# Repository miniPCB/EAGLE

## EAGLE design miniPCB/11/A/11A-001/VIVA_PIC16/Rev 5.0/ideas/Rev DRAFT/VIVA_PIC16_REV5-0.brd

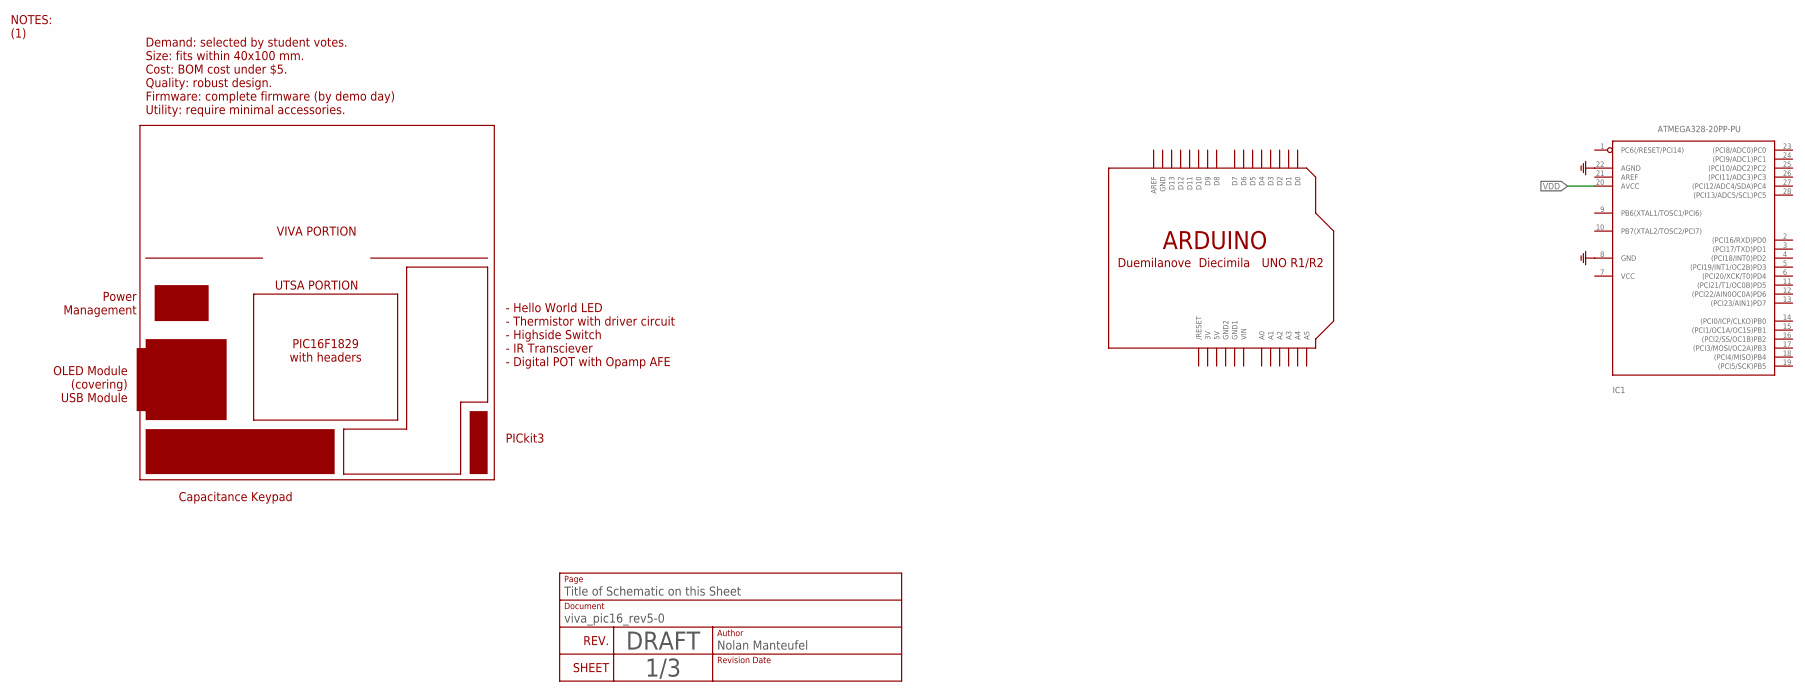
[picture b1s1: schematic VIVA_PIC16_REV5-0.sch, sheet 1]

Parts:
IC1: ATMEGA328-20PP-PU; DIL28-3
U$1: VIVA_LOGO
U$3: ARDUINOUNO; ARDUINO

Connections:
3V: U$3.3V
5V: U$3.5V
GND: IC1.8 (GND), IC1.22 (AGND), U$3.GND; also elsewhere on the board
GND1: U$3.GND1
GND2: U$3.GND2
VDD: IC1.20 (AVCC); also elsewhere on the board
VIN: U$3.VIN

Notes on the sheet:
REV.
DRAFT
Revision Date
Author
SHEET
Document
Title of Schematic on this Sheet
Page
Nolan Manteufel
NOTES: (1)
UTSA PORTION
VIVA PORTION
Demand: selected by student votes. Size: fits within 40x100 mm. Cost: BOM cost under $5. Quality: robust design. Firmware: complete firmware (by demo day) Utility: require minimal accessories.
OLED Module (covering) USB Module
Power Management
Capacitance Keypad
PICkit3
PIC16F1829 with headers
- Hello World LED - Thermistor with driver circuit - Highside Switch - IR Transciever - Digital POT with Opamp AFE

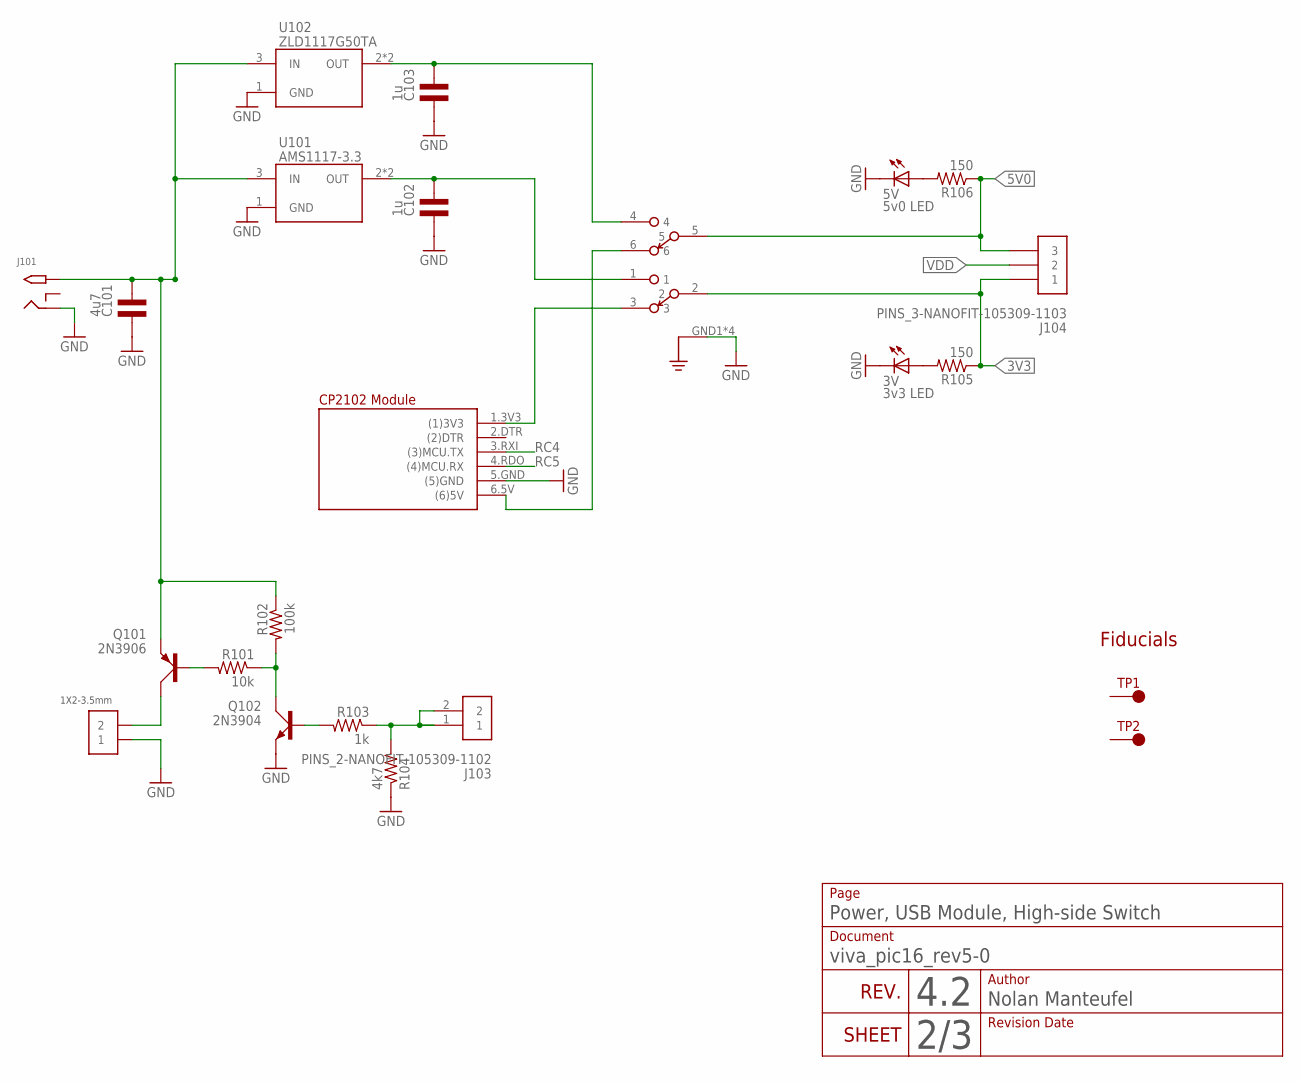
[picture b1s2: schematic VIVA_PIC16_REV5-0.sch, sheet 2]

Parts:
3V: 3v3 LED; CHIPLED_0805
5V: 5v0 LED; CHIPLED_0805
C101: 4u7; C0805
C102, C103: 1u; C0805
J101: 2.1MMJACKTHM; PJ-102A
J102: 1X2-3.5MM-3.5MM; 1X2-3.5MM
J103: PINS_2-NANOFIT-105309-1102; PINS_2-NANOFIT
J104: PINS_3-NANOFIT-105309-1103; PINS_3-NANOFIT
M101: VIVA_USB-TTL; VIVA_USB_TTL_SUBTEXT
Q101: 2N3906; SOT23
Q102: 2N3904; SOT23
R101: 10k; R0805
R102: 100k; R0805
R103: 1k; R0805
R104: 4k7; R0805
R105, R106: 150; R0805
S101: SWITCH_OS202013; OS202013MT5QN1
TP1, TP2: TESTPOINTFIDUCIAL; FIDUCIAL
U101: AMS1117-3.3; SOT223
U102: ZLD1117G50TA; SOT223

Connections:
3V3: J104.1, R105.1, S101.2
5V0: J104.3, R106.1, S101.5
GND: 3V.C, 5V.C, C101.1, C102.1, C103.1, J101.RING, J102.1, M101.5.GND ((5)GND), Q102.2 (E), R104.1, S101.GND1 (GND), S101.GND2 (GND), S101.GND3 (GND), S101.GND4 (GND), U101.1 (GND), U102.1 (GND); also elsewhere on the board
unnamed: J103.1, J103.2, R103.1, R104.2
unnamed: 5V.A, R106.2
unnamed: Q101.1 (B), R101.2
unnamed: Q102.3 (C), R101.1, R102.2
unnamed: Q102.1 (B), R103.2
unnamed: M101.1.3V3 ((1)3V3), S101.3
unnamed: J102.2, Q101.3 (C)
unnamed: M101.6.5V ((6)5V), S101.6
unnamed: C103.2, S101.4, U102.2 (OUT), U102.4.TAB (OUT)
unnamed: C102.2, S101.1, U101.2 (OUT), U101.4.TAB (OUT)
unnamed: 3V.A, R105.2
RC4: M101.3.RXI ((3)MCU.TX); also elsewhere on the board
RC5: M101.4.RDO ((4)MCU.RX); also elsewhere on the board
VDC: C101.2, J101.TIP, Q101.2 (E), R102.1, U101.3 (IN), U102.3 (IN)
VDD: J104.2; also elsewhere on the board

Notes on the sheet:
REV.
4.2
Revision Date
Author
SHEET
Document
Power, USB Module, High-side Switch
Page
Nolan Manteufel
Fiducials

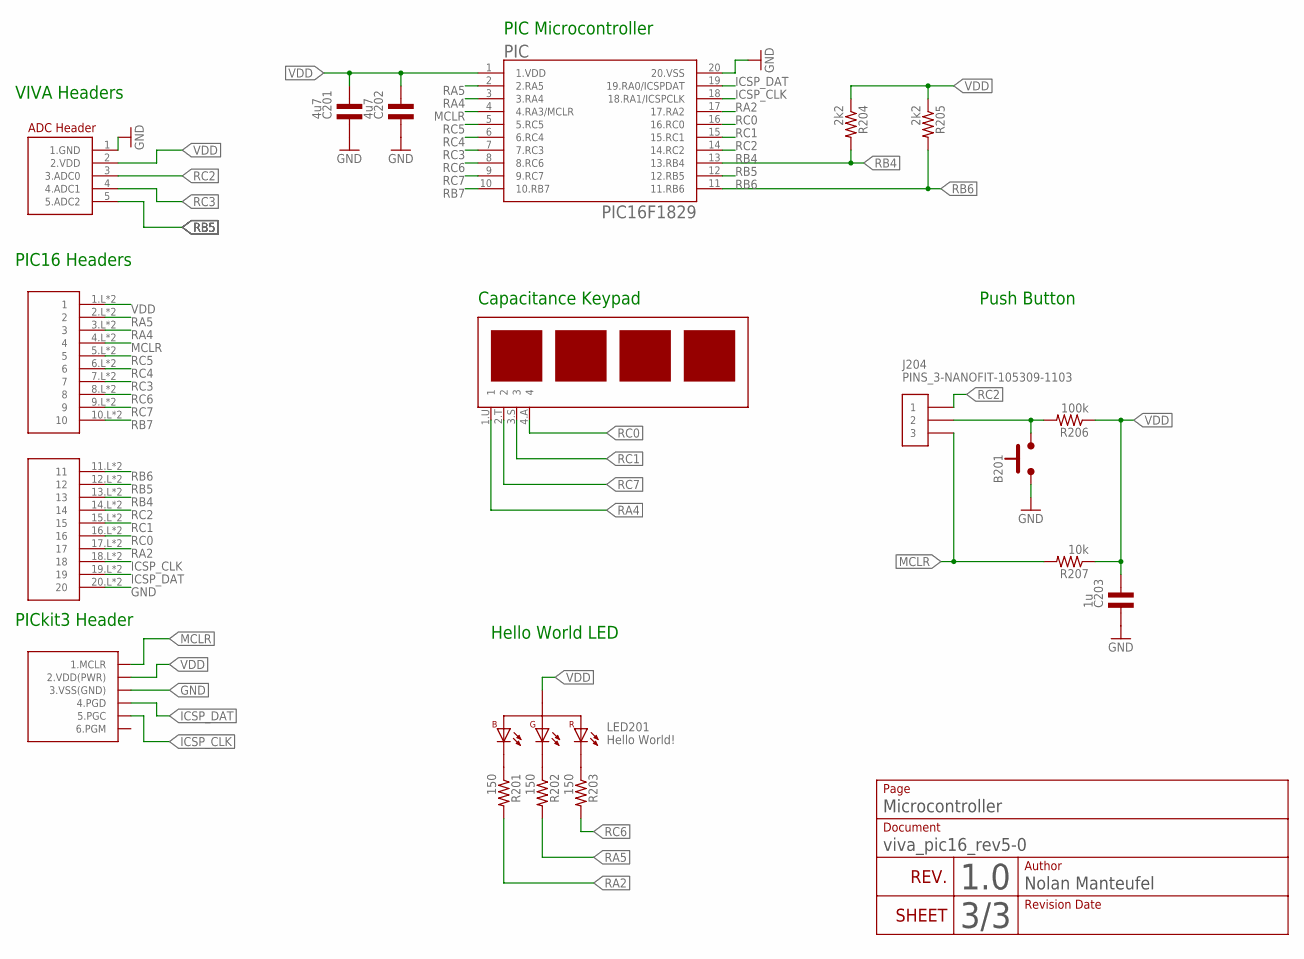
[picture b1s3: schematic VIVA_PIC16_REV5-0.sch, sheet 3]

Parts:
B201: PUSHBUTTON6X6MM; 6X6MM
C201, C202: 4u7; C0805
C203: 1u; C0805
J201: VIVA_PIC16
J202: VIVA-HEADER-ADCNONAME; VIVA-HEADER-ADC-NONAME
J203: PICKIT3
J204: PINS_3-NANOFIT-105309-1103; PINS_3-NANOFIT
LED201: Hello World!; 0805_RGB
PIC: PIC16F1829; SOP20-NEW
R201, R202, R203: 150; R0805
R204, R205: 2k2; R0805
R206: 100k; R0805
R207: 10k; R0805
U$201: VIVA_UTSA-KEYPAD

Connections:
GND: B201.1.A (1), B201.2.A (1), C201.1, C202.1, C203.1, J201.20.L (20), J201.20.R (20), J202.1 (1.GND), J203.3 (3.VSS(GND)), PIC.20 (20.VSS); also elsewhere on the board
ICSP_CLK: J201.18.L (18), J201.18.R (18), J203.5 (5.PGC), PIC.18 (18.RA1/ICSPCLK)
ICSP_DAT: J201.19.L (19), J201.19.R (19), J203.4 (4.PGD), PIC.19 (19.RA0/ICSPDAT)
MCLR: J201.4.L (4), J201.4.R (4), J203.1 (1.MCLR), J204.3, PIC.4 (4.RA3/MCLR), R207.2
unnamed: B201.3.B (2), B201.4.B (2), J204.2, R206.2
unnamed: LED201.1 (4.B-), R201.1
unnamed: LED201.3 (2.G-), R202.1
unnamed: LED201.2 (1.R-), R203.1
RA2: J201.17.L (17), J201.17.R (17), PIC.17 (17.RA2), R201.2
RA4: J201.3.L (3), J201.3.R (3), PIC.3 (3.RA4), U$201.1.U (1)
RA5: J201.2.L (2), J201.2.R (2), PIC.2 (2.RA5), R202.2
RB4: J201.13.L (13), J201.13.R (13), PIC.13 (13.RB4), R204.2
RB5: J201.12.L (12), J201.12.R (12), J202.5 (5.ADC2), PIC.12 (12.RB5)
RB6: J201.11.L (11), J201.11.R (11), PIC.11 (11.RB6), R205.2
RB7: J201.10.L (10), J201.10.R (10), PIC.10 (10.RB7)
RC0: J201.16.L (16), J201.16.R (16), PIC.16 (16.RC0), U$201.4.A (4)
RC1: J201.15.L (15), J201.15.R (15), PIC.15 (15.RC1), U$201.3.S (3)
RC2: J201.14.L (14), J201.14.R (14), J202.3 (3.ADC0), J204.1, PIC.14 (14.RC2)
RC3: J201.7.L (7), J201.7.R (7), J202.4 (4.ADC1), PIC.7 (7.RC3)
RC4: J201.6.L (6), J201.6.R (6), PIC.6 (6.RC4); also elsewhere on the board
RC5: J201.5.L (5), J201.5.R (5), PIC.5 (5.RC5); also elsewhere on the board
RC6: J201.8.L (8), J201.8.R (8), PIC.8 (8.RC6), R203.2
RC7: J201.9.L (9), J201.9.R (9), PIC.9 (9.RC7), U$201.2.T (2)
VDD: C201.2, C202.2, C203.2, J201.1.L (1), J201.1.R (1), J202.2 (2.VDD), J203.2 (2.VDD(PWR)), LED201.4 (3.+), PIC.1 (1.VDD), R204.1, R205.1, R206.1, R207.1; also elsewhere on the board

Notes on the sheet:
REV.
1.0
Revision Date
Author
SHEET
Document
Microcontroller
Page
Nolan Manteufel
Push Button
Hello World LED
PICkit3 Header
PIC Microcontroller
VIVA Headers
PIC16 Headers
Capacitance Keypad

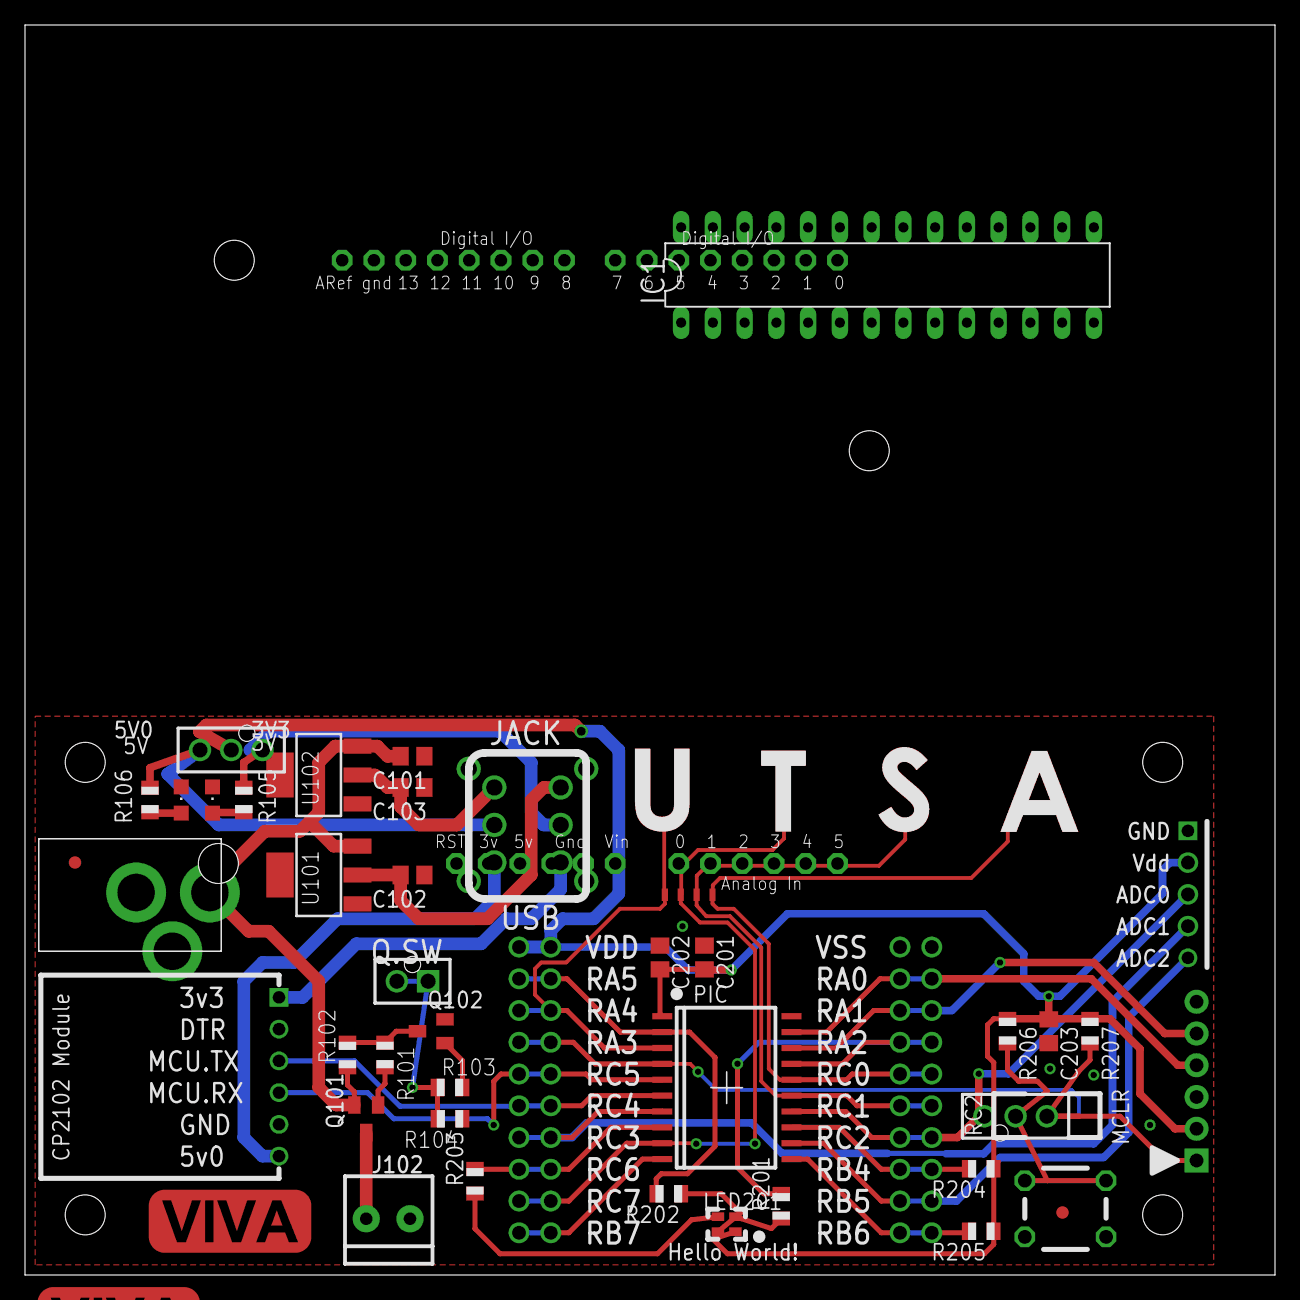
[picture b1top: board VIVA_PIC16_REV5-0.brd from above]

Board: 2 copper layers, 100.0 x 100.0 mm, 45 parts (0 on the bottom side), 38 nets.

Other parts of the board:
U$2: VIVA_LOGO

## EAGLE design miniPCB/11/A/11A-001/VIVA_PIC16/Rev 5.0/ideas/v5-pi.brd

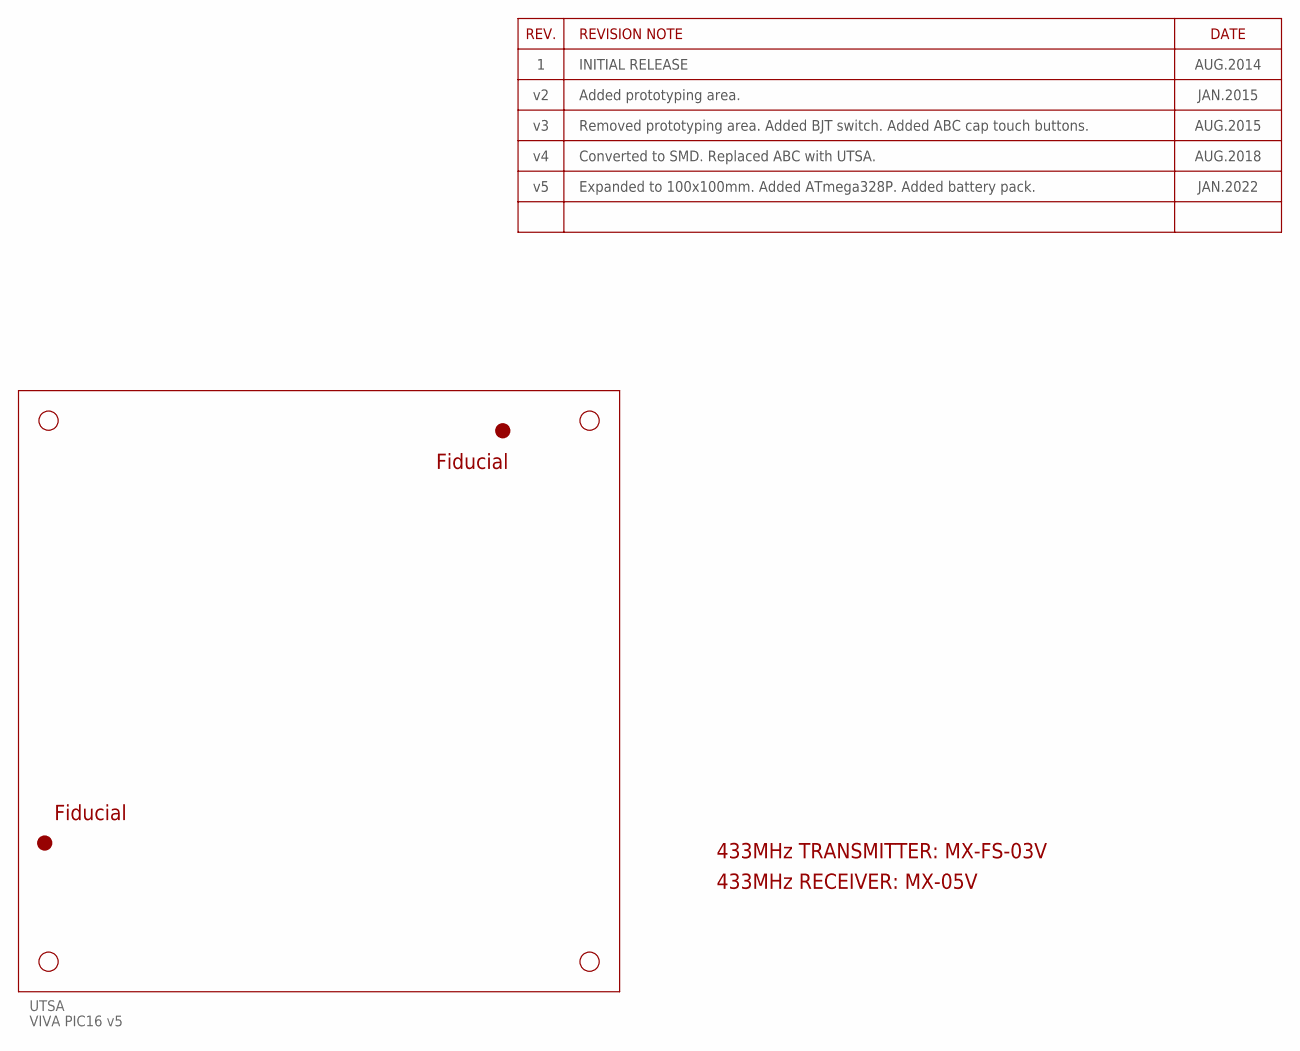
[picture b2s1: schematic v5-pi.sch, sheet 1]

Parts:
FIDUCIAL1, FIDUCIAL2: FIDUCIAL
UTSA: VIVA PIC16 v5; PCB_100X100

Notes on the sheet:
Fiducial
433MHz TRANSMITTER: MX-FS-03V
433MHz RECEIVER: MX-05V

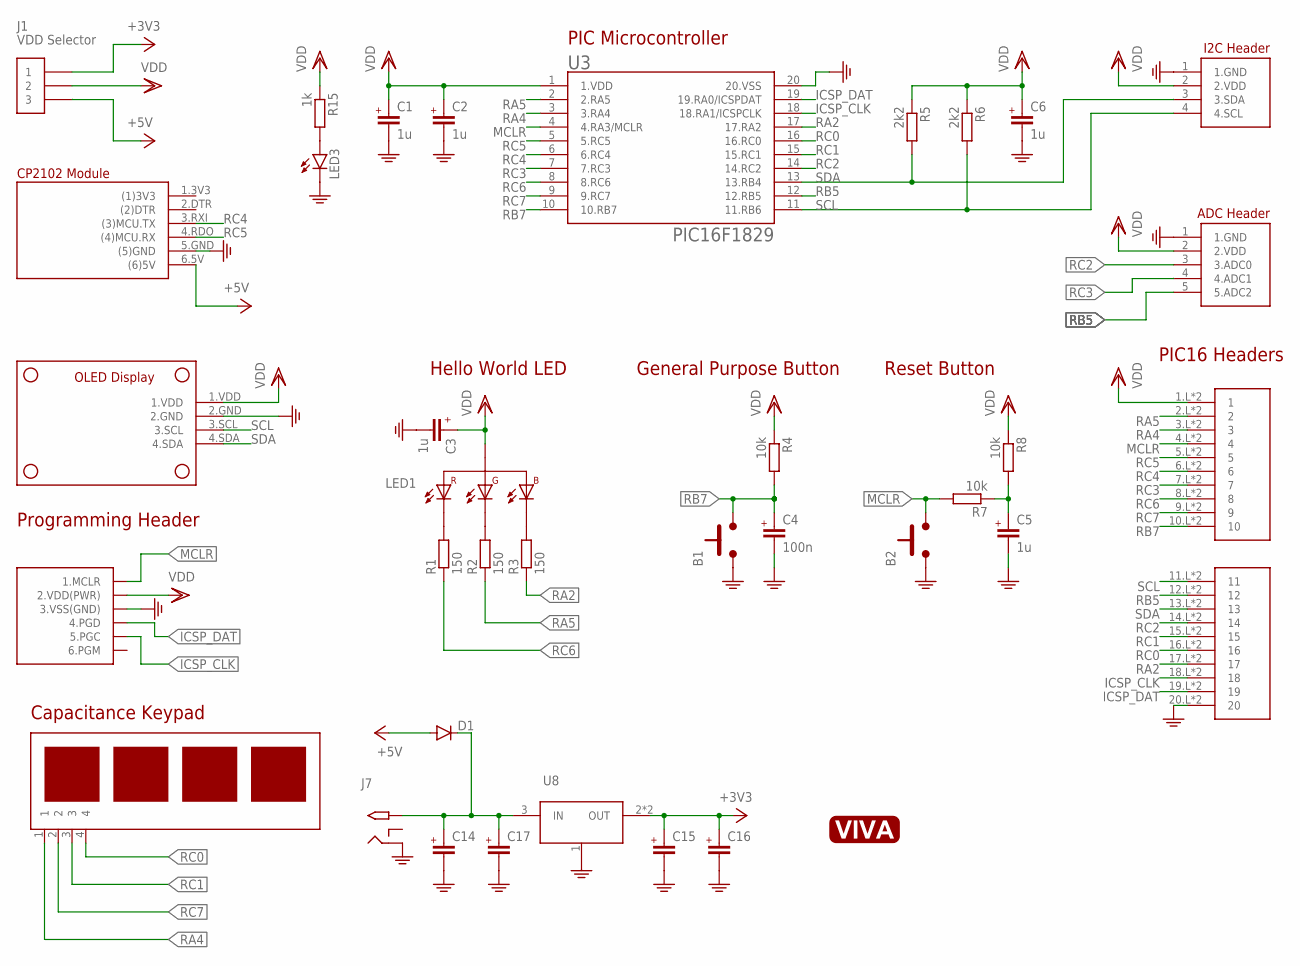
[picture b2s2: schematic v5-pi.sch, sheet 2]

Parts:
B1, B2: PUSHBUTTON6X6MM; 6X6MM
C1, C2, C3, C5, C6: 1u; C0805
C4: 100n; C0805
C14, C15, C16, C17: C0805
D1: DIODE-DO214AC; DO214AC
J1: VDD Selector; PINS_3
J4: PICKIT3
J5: VIVA-HEADER-ADC-PIC16
J7: 2.1MMJACKTHM; PJ-102A
LED1: LED_RGBLTST-C19FD1WT; 0805_RGB
LED3: LEDSML0805; SML0805
R1, R2, R3: 150; R0805
R4, R7, R8: 10k; R0805
R5, R6: 2k2; R0805
R15: 1k; R0805
U1: VIVA_UTSA-KEYPADV5; VIVA_UTSA-KEYPAD-V5
U2: VIVA_USB-TTL; VIVA_USB_TTL_SUBTEXT
U3: PIC16F1829; SOP20-NEW
U4: VIVA-HEADER-I2C-RA
U5: VIVA_PIC16BOARD; VIVA_PIC16
U8: REGULATOR_SCHLM1117; SOT223
U$2: VIVA_LOGO
U$3: VIVA_OLED; VIVA_OLED-I2C

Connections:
+3V3: C15.2 (+), C16.2 (+), J1.1, U8.2 (OUT), U8.4.TAB (OUT)
+5V: D1.A, J1.3, U2.6.5V ((6)5V); also elsewhere on the board
GND: B1.1.A (1), B1.2.A (1), B2.1.A (1), B2.2.A (1), C1.1 (-), C2.1 (-), C3.1 (-), C4.1 (-), C5.1 (-), C6.1 (-), C14.1 (-), C15.1 (-), C16.1 (-), C17.1 (-), J4.3 (3.VSS(GND)), J5.1 (1.GND), J7.RING, LED3.C, U2.5.GND ((5)GND), U3.20 (20.VSS), U4.1 (1.GND), U5.20.L (20), U5.20.R (20), U8.1 (GND), U$3.2.GND; also elsewhere on the board
ICSP_CLK: J4.5 (5.PGC), U3.18 (18.RA1/ICSPCLK), U5.18.L (18), U5.18.R (18)
ICSP_DAT: J4.4 (4.PGD), U3.19 (19.RA0/ICSPDAT), U5.19.L (19), U5.19.R (19)
MCLR: B2.3.B (2), B2.4.B (2), J4.1 (1.MCLR), R7.2, U3.4 (4.RA3/MCLR), U5.4.L (4), U5.4.R (4)
MCLR_CAP: C5.2 (+), R7.1, R8.2
unnamed: LED1.2 (1.R-), R1.2
unnamed: LED1.3 (2.G-), R2.2
unnamed: LED1.1 (4.B-), R3.2
unnamed: C14.2 (+), C17.2 (+), D1.C, J7.TIP, U8.3 (IN)
unnamed: LED3.A, R15.2
RA2: R3.1, U3.17 (17.RA2), U5.17.L (17), U5.17.R (17)
RA4: U1.1, U3.3 (3.RA4), U5.3.L (3), U5.3.R (3)
RA5: R2.1, U3.2 (2.RA5), U5.2.L (2), U5.2.R (2)
RB5: J5.5 (5.ADC2), U3.12 (12.RB5), U5.12.L (12), U5.12.R (12)
RB7: B1.3.B (2), B1.4.B (2), C4.2 (+), R4.2, U3.10 (10.RB7), U5.10.L (10), U5.10.R (10)
RC0: U1.4, U3.16 (16.RC0), U5.16.L (16), U5.16.R (16)
RC1: U1.3, U3.15 (15.RC1), U5.15.L (15), U5.15.R (15)
RC2: J5.3 (3.ADC0), U3.14 (14.RC2), U5.14.L (14), U5.14.R (14)
RC3: J5.4 (4.ADC1), U3.7 (7.RC3), U5.7.L (7), U5.7.R (7)
RC4: U2.3.RXI ((3)MCU.TX), U3.6 (6.RC4), U5.6.L (6), U5.6.R (6)
RC5: U2.4.RDO ((4)MCU.RX), U3.5 (5.RC5), U5.5.L (5), U5.5.R (5)
RC6: R1.1, U3.8 (8.RC6), U5.8.L (8), U5.8.R (8)
RC7: U1.2, U3.9 (9.RC7), U5.9.L (9), U5.9.R (9)
SCL: R6.2, U3.11 (11.RB6), U4.4 (4.SCL), U5.11.L (11), U5.11.R (11), U$3.3.SCL; also elsewhere on the board
SDA: R5.2, U3.13 (13.RB4), U4.3 (3.SDA), U5.13.L (13), U5.13.R (13), U$3.4.SDA; also elsewhere on the board
VDD: C1.2 (+), C2.2 (+), C3.2 (+), C6.2 (+), J1.2, J4.2 (2.VDD(PWR)), J5.2 (2.VDD), LED1.4 (3.+), R4.1, R5.1, R6.1, R8.1, R15.1, U3.1 (1.VDD), U4.2 (2.VDD), U5.1.L (1), U5.1.R (1), U$3.1.VDD; also elsewhere on the board

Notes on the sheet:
General Purpose Button
Hello World LED
PIC Microcontroller
Capacitance Keypad
Reset Button
Programming Header
PIC16 Headers

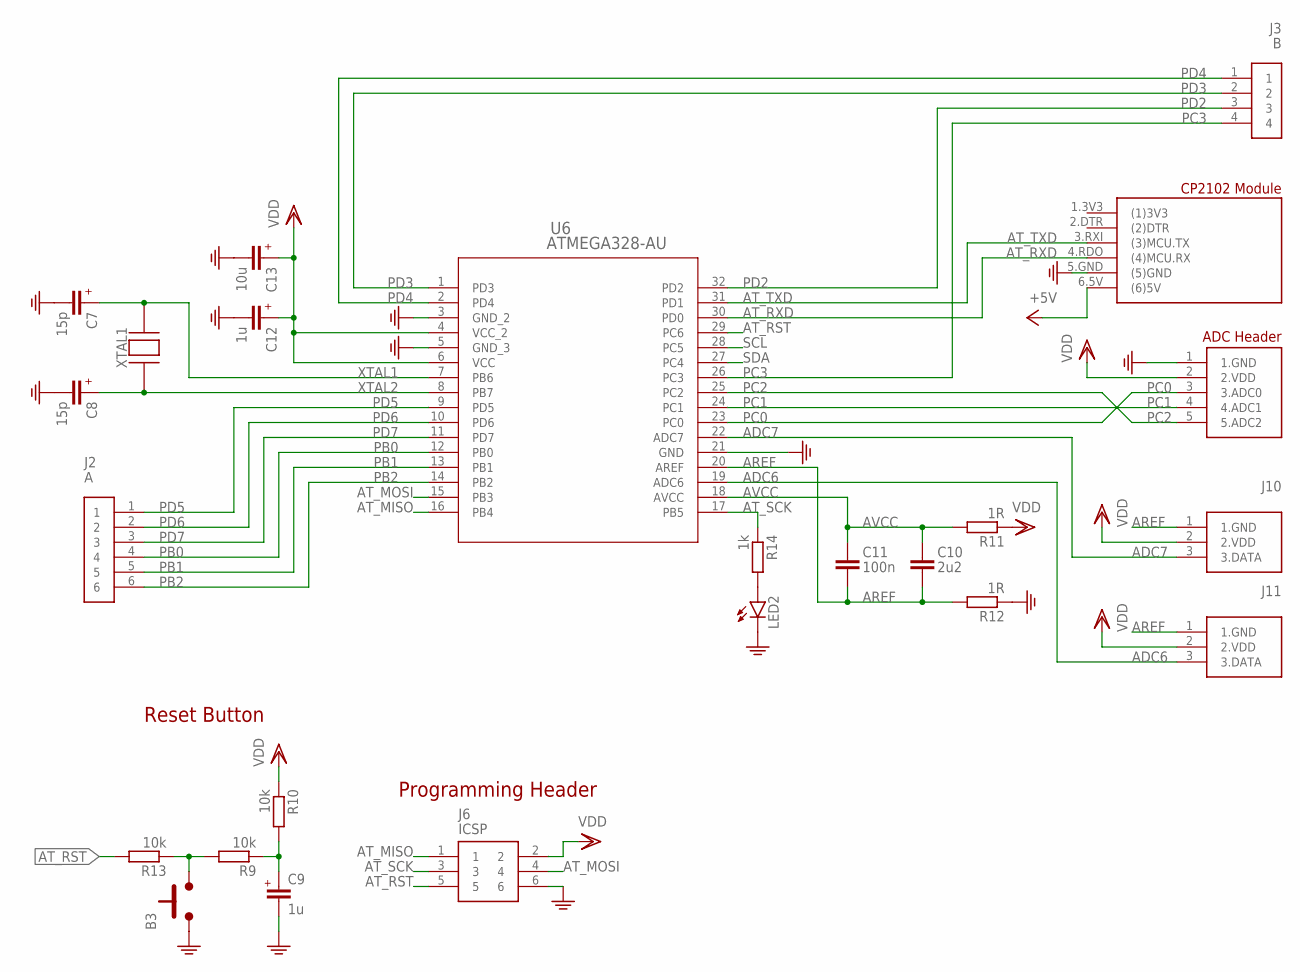
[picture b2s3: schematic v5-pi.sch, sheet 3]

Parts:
B3: PUSHBUTTON6X6MM; 6X6MM
C7, C8: 15p; C0603
C9, C12: 1u; C0805
C10: 2u2; C0805
C11: 100n; C0805
C13: 10u; C0805
J2: A; PINS_6
J3: B; PINS_4
J6: ICSP; PINS_6-2X3
J9: VIVA-HEADER-ADC-PIC16
J10, J11: VIVA-HEADER-GPIO-1; VIVA-HEADER-GPIO-RA-1
LED2: LEDSML0805; SML0805
R9, R10, R13: 10k; R0805
R11, R12: 1R; R0805
R14: 1k; R0805
U6: ATMEGA328-AU; 32A_ATM
U7: VIVA_USB-TTL; VIVA_USB_TTL_SUBTEXT
XTAL1: CRYSTAL-SMD; HC49S-SMD

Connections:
+5V: U7.6.5V ((6)5V); also elsewhere on the board
ADC6: J11.3 (3.DATA), U6.19 (ADC6)
ADC7: J10.3 (3.DATA), U6.22 (ADC7)
AREF: C10.2, C11.2, J10.1 (1.GND), J11.1 (1.GND), R12.2, U6.20 (AREF)
AT_MISO: J6.1, U6.16 (PB4)
AT_MOSI: J6.4, U6.15 (PB3)
AT_RST: J6.5, R13.2, U6.29 (PC6)
AT_RST_BTN: B3.3.B (2), B3.4.B (2), R9.2, R13.1
AT_RST_CAP: C9.2 (+), R9.1, R10.2
AT_RXD: U6.30 (PD0), U7.4.RDO ((4)MCU.RX)
AT_SCK: J6.3, R14.1, U6.17 (PB5)
AT_TXD: U6.31 (PD1), U7.3.RXI ((3)MCU.TX)
AVCC: C10.1, C11.1, R11.2, U6.18 (AVCC)
GND: B3.1.A (1), B3.2.A (1), C7.1 (-), C8.1 (-), C9.1 (-), C12.1 (-), C13.1 (-), J6.6, J9.1 (1.GND), LED2.C, R12.1, U6.3 (GND_2), U6.5 (GND_3), U6.21 (GND), U7.5.GND ((5)GND); also elsewhere on the board
unnamed: LED2.A, R14.2
PB0: J2.4, U6.12 (PB0)
PB1: J2.5, U6.13 (PB1)
PB2: J2.6, U6.14 (PB2)
PC0: J9.3 (3.ADC0), U6.23 (PC0)
PC1: J9.4 (4.ADC1), U6.24 (PC1)
PC2: J9.5 (5.ADC2), U6.25 (PC2)
PC3: J3.4, U6.26 (PC3)
PD2: J3.3, U6.32 (PD2)
PD3: J3.2, U6.1 (PD3)
PD4: J3.1, U6.2 (PD4)
PD5: J2.1, U6.9 (PD5)
PD6: J2.2, U6.10 (PD6)
PD7: J2.3, U6.11 (PD7)
SCL: U6.28 (PC5); also elsewhere on the board
SDA: U6.27 (PC4); also elsewhere on the board
VDD: C12.2 (+), C13.2 (+), J6.2, J9.2 (2.VDD), J10.2 (2.VDD), J11.2 (2.VDD), R10.1, R11.1, U6.4 (VCC_2), U6.6 (VCC); also elsewhere on the board
XTAL1: C7.2 (+), U6.7 (PB6), XTAL1.2, XTAL1.4 (2)
XTAL2: C8.2 (+), U6.8 (PB7), XTAL1.1, XTAL1.3 (1)

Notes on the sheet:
Reset Button
Programming Header

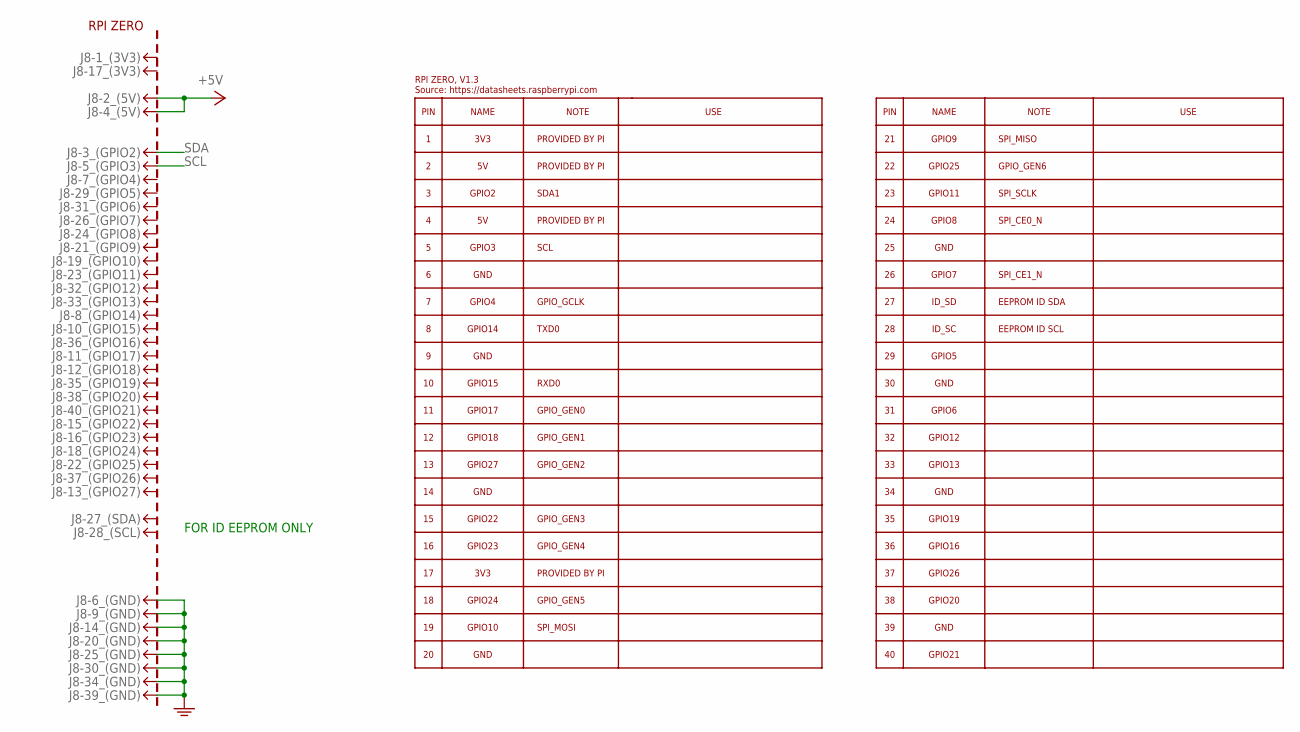
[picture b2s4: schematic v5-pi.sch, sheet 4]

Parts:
J8-: RPI ZERO; RPI_ZERO

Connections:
+5V: J8-.2, J8-.4; also elsewhere on the board
GND: J8-.6, J8-.9, J8-.14, J8-.20, J8-.25, J8-.30, J8-.34, J8-.39; also elsewhere on the board
SCL: J8-.5; also elsewhere on the board
SDA: J8-.3; also elsewhere on the board

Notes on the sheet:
FOR ID EEPROM ONLY

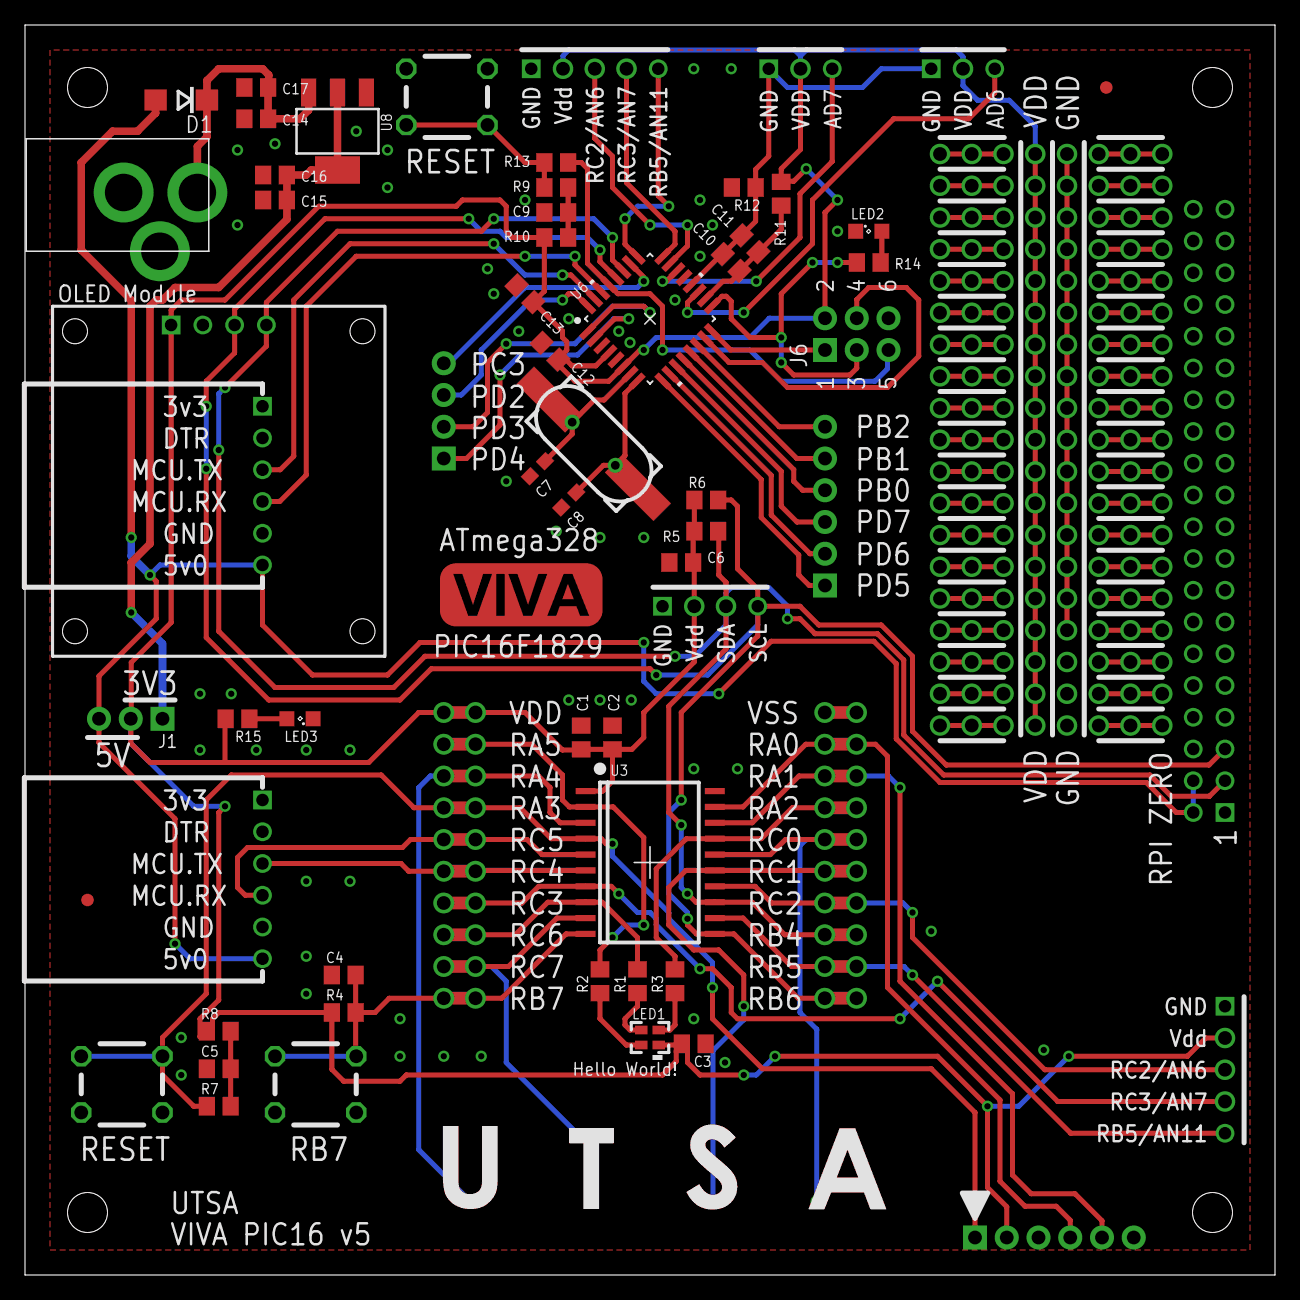
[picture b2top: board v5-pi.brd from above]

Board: 4 copper layers, 100.0 x 100.0 mm, 64 parts (0 on the bottom side), 56 nets.

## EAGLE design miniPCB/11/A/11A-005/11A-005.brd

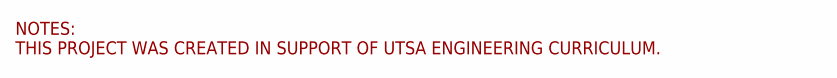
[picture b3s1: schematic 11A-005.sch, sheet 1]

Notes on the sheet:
NOTES: THIS PROJECT WAS CREATED IN SUPPORT OF UTSA ENGINEERING CURRICULUM.

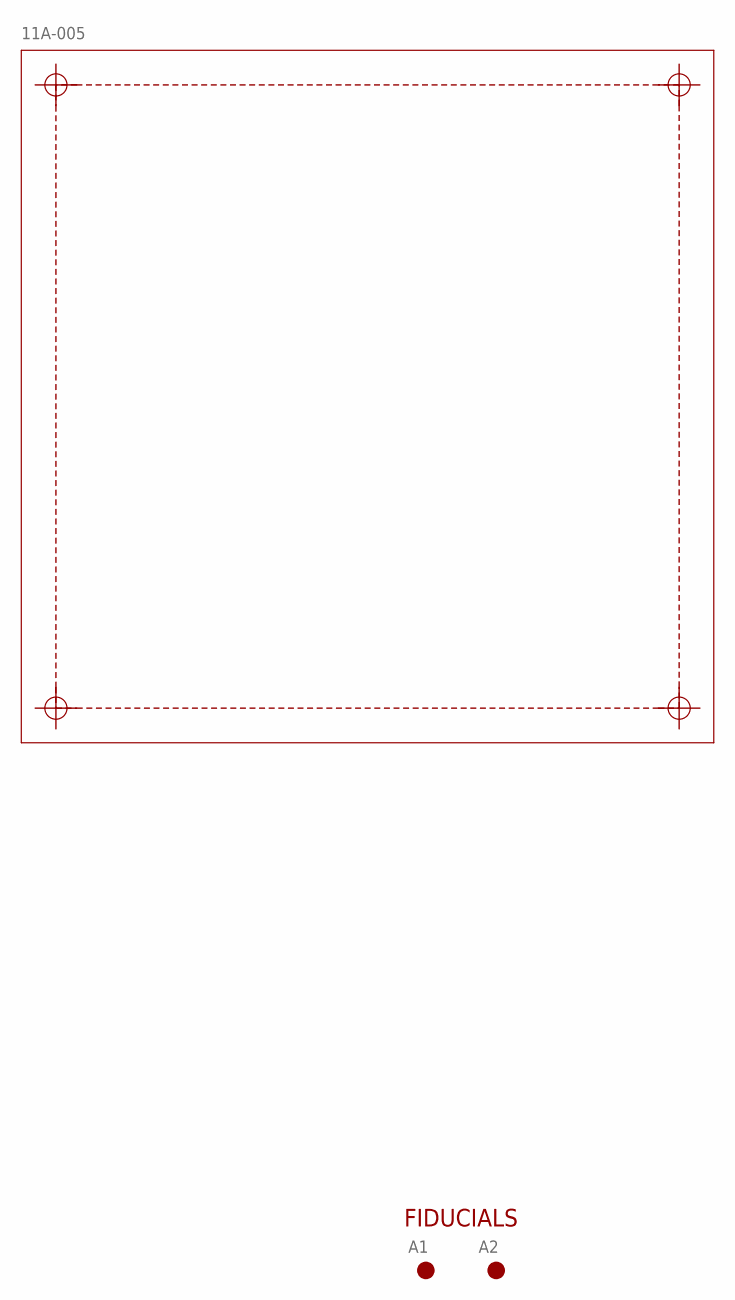
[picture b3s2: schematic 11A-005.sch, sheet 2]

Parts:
-: 11A-005; PCB_100X100
A1, A2: FIDUCIAL

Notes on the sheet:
FIDUCIALS

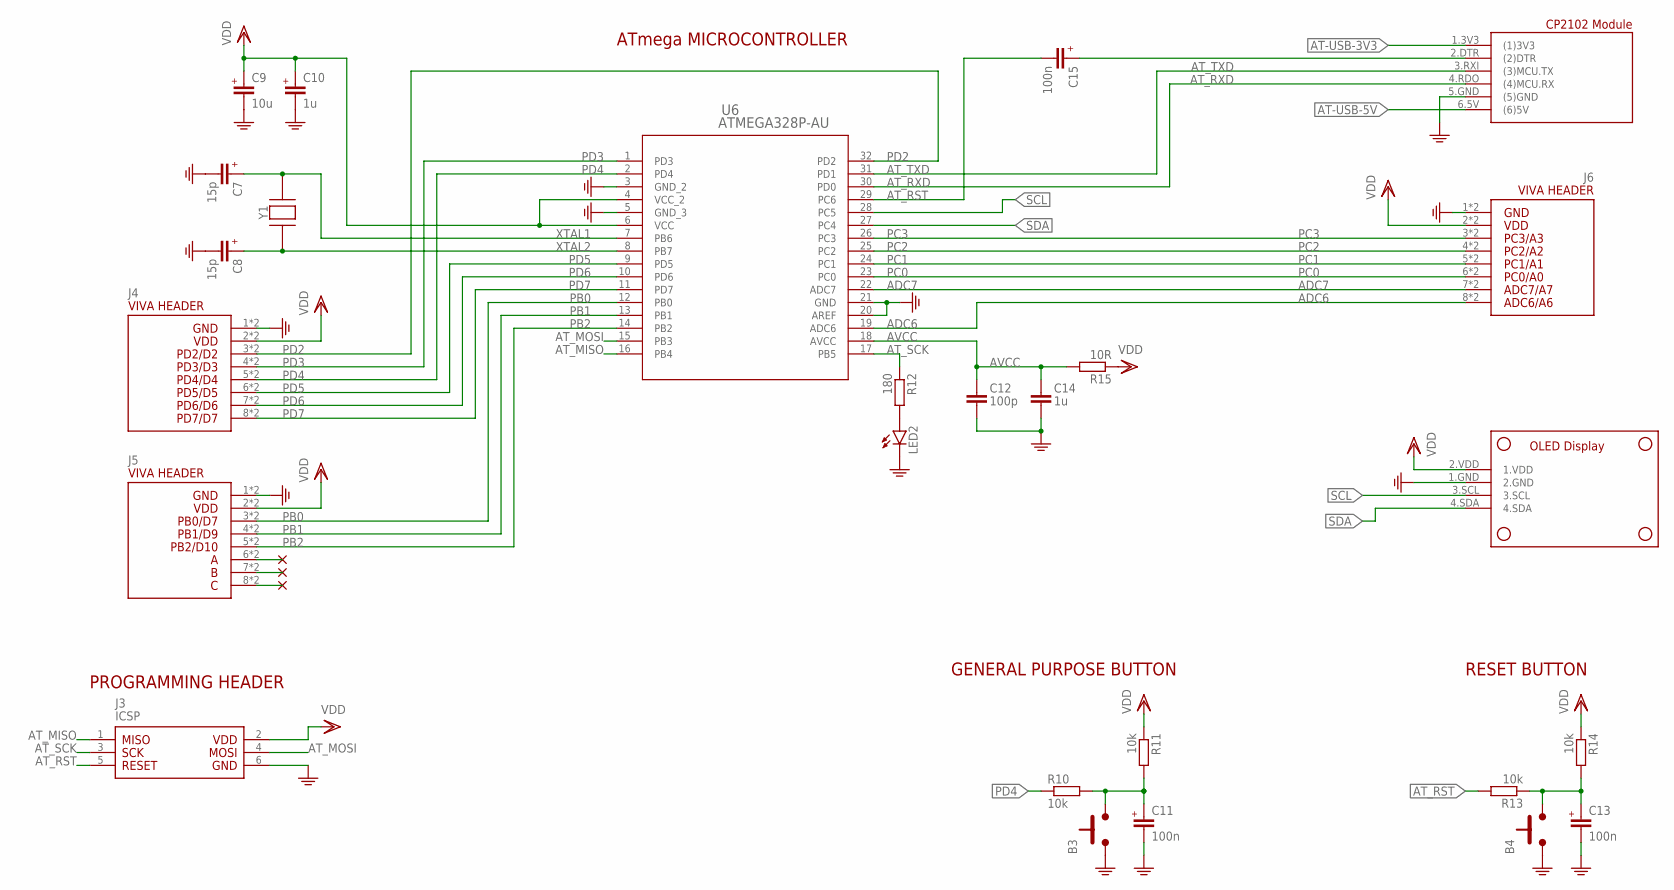
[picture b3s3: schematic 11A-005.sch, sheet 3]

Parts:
$3_73_$: VIVA_OLEDGND; VIVA_OLED-I2C-ALT
B3, B4: PUSHBUTTON6X6MM; 6X6MM
C7, C8: 15p; C0603
C9: 10u; C0805
C10, C14: 1u; C0805
C11, C13, C15: 100n; C0805
C12: 100p; C0805
J3: ICSP; PINS_6-2X3_AT
J4, J5, J6: VIVA-HEADER-ADC-8P
LED2: LEDSML0805; SML0805
R10, R11, R13, R14: 10k; R0805
R12: 180; R0805
R15: 10R; R0805
U6: ATMEGA328P-AU; 32A_ATM
U7: VIVA_USB-TTL; VIVA_USB_TTL_SUBTEXT
Y1: CRYSTAL-3225_4P; TXC7M2

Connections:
ADC6: J6.8 (8.ADC5), J6.9 (8.ADC5), U6.19 (ADC6)
ADC7: J6.7 (7.ADC4), J6.10 (7.ADC4), U6.22 (ADC7)
AT-USB-3V3: U7.1.3V3 ((1)3V3); also elsewhere on the board
AT-USB-5V: U7.6.5V ((6)5V); also elsewhere on the board
AT_DTR_CAP: C15.1 (+), U7.2.DTR ((2)DTR)
AT_MISO: J3.1, U6.16 (PB4)
AT_MOSI: J3.4, U6.15 (PB3)
AT_RST: C15.2 (-), J3.5, R13.2, U6.29 (PC6)
AT_RST_CAP: B4.3.B (2), B4.4.B (2), C13.1 (+), R13.1, R14.2
AT_RXD: U6.30 (PD0), U7.4.RDO ((4)MCU.RX)
AT_SCK: J3.3, R12.1, U6.17 (PB5)
AT_TXD: U6.31 (PD1), U7.3.RXI ((3)MCU.TX)
AVCC: C12.1, C14.1, R15.2, U6.18 (AVCC)
GND: $3_73_$.1.GND (2.GND), B3.1.A (1), B3.2.A (1), B4.1.A (1), B4.2.A (1), C7.1 (-), C8.1 (-), C9.2 (-), C10.2 (-), C11.2 (-), C12.2, C13.2 (-), C14.2, J3.6, J4.1 (1.GND), J4.16 (1.GND), J5.1 (1.GND), J5.16 (1.GND), J6.1 (1.GND), J6.16 (1.GND), LED2.C, U6.3 (GND_2), U6.5 (GND_3), U6.20 (AREF), U6.21 (GND), U7.5.GND ((5)GND); also elsewhere on the board
unnamed: J5.6 (6.ADC3), J5.11 (6.ADC3)
unnamed: J5.7 (7.ADC4), J5.10 (7.ADC4)
unnamed: J5.8 (8.ADC5), J5.9 (8.ADC5)
unnamed: LED2.A, R12.2
PB0: J5.3 (3.ADC0), J5.14 (3.ADC0), U6.12 (PB0)
PB1: J5.4 (4.ADC1), J5.13 (4.ADC1), U6.13 (PB1)
PB2: J5.5 (5.ADC2), J5.12 (5.ADC2), U6.14 (PB2)
PC0: J6.6 (6.ADC3), J6.11 (6.ADC3), U6.23 (PC0)
PC1: J6.5 (5.ADC2), J6.12 (5.ADC2), U6.24 (PC1)
PC2: J6.4 (4.ADC1), J6.13 (4.ADC1), U6.25 (PC2)
PC3: J6.3 (3.ADC0), J6.14 (3.ADC0), U6.26 (PC3)
PD2: J4.3 (3.ADC0), J4.14 (3.ADC0), U6.32 (PD2)
PD3: J4.4 (4.ADC1), J4.13 (4.ADC1), U6.1 (PD3)
PD4: J4.5 (5.ADC2), J4.12 (5.ADC2), R10.1, U6.2 (PD4)
PD4-CAP: B3.3.B (2), B3.4.B (2), C11.1 (+), R10.2, R11.2
PD5: J4.6 (6.ADC3), J4.11 (6.ADC3), U6.9 (PD5)
PD6: J4.7 (7.ADC4), J4.10 (7.ADC4), U6.10 (PD6)
PD7: J4.8 (8.ADC5), J4.9 (8.ADC5), U6.11 (PD7)
SCL: $3_73_$.3.SCL, U6.28 (PC5)
SDA: $3_73_$.4.SDA, U6.27 (PC4)
VDD: $3_73_$.2.VDD (1.VDD), C9.1 (+), C10.1 (+), J3.2, J4.2 (2.VDD), J4.15 (2.VDD), J5.2 (2.VDD), J5.15 (2.VDD), J6.2 (2.VDD), J6.15 (2.VDD), R11.1, R14.1, R15.1, U6.4 (VCC_2), U6.6 (VCC); also elsewhere on the board
XTAL1: C7.2 (+), U6.7 (PB6), Y1.3 (2)
XTAL2: C8.2 (+), U6.8 (PB7), Y1.1

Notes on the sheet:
PROGRAMMING HEADER
ATmega MICROCONTROLLER
RESET BUTTON
GENERAL PURPOSE BUTTON

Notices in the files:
parts and their libraries:
COPYRIGHT: Copyright (C) 2021 Ultra Librarian. All rights reserved.
